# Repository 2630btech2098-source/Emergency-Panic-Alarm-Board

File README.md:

# Emergency Panic Alarm Board

**Student: Mohak Saxena**  
KiCad 10 PCB design project | Revision 1.0

## Overview

A regulated 5 V, momentary push-to-sound alarm. Holding the normally-open panic button activates an internally driven buzzer and a red warning LED. Releasing the button turns both off. There is no latching/reset function.

The supplied brief contained a conflicting water-level-indicator sentence. This project follows its Emergency Panic Alarm Board title, alarm scenario, and listed components.

## Circuit

- **J1:** 2-pin, 5.08 mm power terminal; pin 1 = +5 V and pin 2 = GND.
- **SW1:** Normally-open, 6 mm through-hole push button.
- **BZ1:** CEM-1205-IC or mechanically/electrically compatible **active 5 V** buzzer; a passive transducer is not suitable without an oscillator.
- **R1:** 330 ohms, 0.25 W axial resistor.
- **D1:** Red 5 mm LED. With an assumed 2 V forward voltage, nominal LED current is approximately 9.1 mA.

Board: **50 x 38 mm**, two copper layers, 0.6 mm tracks, through-hole components, no vias.

## Files

| File | Purpose |
| --- | --- |
| `Emergency_Panic_Alarm_Board.kicad_pro` | KiCad project |
| `Emergency_Panic_Alarm_Board.kicad_sch` | Editable schematic |
| `Emergency_Panic_Alarm_Board.kicad_pcb` | Routed PCB |
| `Mohak_Saxena_Emergency_Panic_Alarm_Board_Report.pdf` | Six-page report with schematic, routed footprints, 2D/3D views, BOM and verification |
| `Mohak_Saxena_BOM.csv` | Bill of materials exported from KiCad |
| `Mohak_Saxena_PCB_Routed.png` | PCB Editor capture |
| `Mohak_Saxena_PCB_3D.png` | KiCad 3D Viewer export |
| `Mohak_Saxena_Gerbers.zip` | Gerber layers, job file and Excellon drill files |
| `Mohak_Saxena_KiCad_Project_and_Gerbers.zip` | Downloadable project/report/fabrication package |

Open the `.kicad_pro` file in KiCad 10. Standard KiCad symbol, footprint and 3D model libraries are required. If 3D models are not found on another computer, relink their paths to that computer's KiCad model library; model paths do not affect the copper design.

## Verification

KiCad's Electrical Rules Check reported **0 errors and 0 warnings**. The PCB Design Rules Check reported **0 errors, 0 warnings, 0 unconnected items and 0 schematic/PCB parity issues**, using project/default rule settings. The board was also inspected in KiCad's 3D Viewer.

## Fabrication and testing limits

**Educational prototype only - not a certified emergency or life-safety alarm.**

No physical assembly, bench testing or sound-level measurement has been performed. There is no battery backup, fault supervision, reverse-polarity protection or latched alarm. Before fabrication, confirm the purchased components' pin spacing, polarity, switch pin grouping, voltage/current ratings, enclosure fit and manufacturer capabilities. Use a current-limited regulated 5 V source during initial testing and inspect for shorts before applying power.

The Gerber archive includes front/back copper, solder mask and silkscreen, Edge.Cuts, a Gerber job file, and separate plated/non-plated Excellon drill files. Empty paste layers are included for this through-hole design.

## Reference

[Same Sky CEM-1205-IC manufacturer datasheet](https://www.sameskydevices.com/product/resource/cem-1205-ic.pdf)

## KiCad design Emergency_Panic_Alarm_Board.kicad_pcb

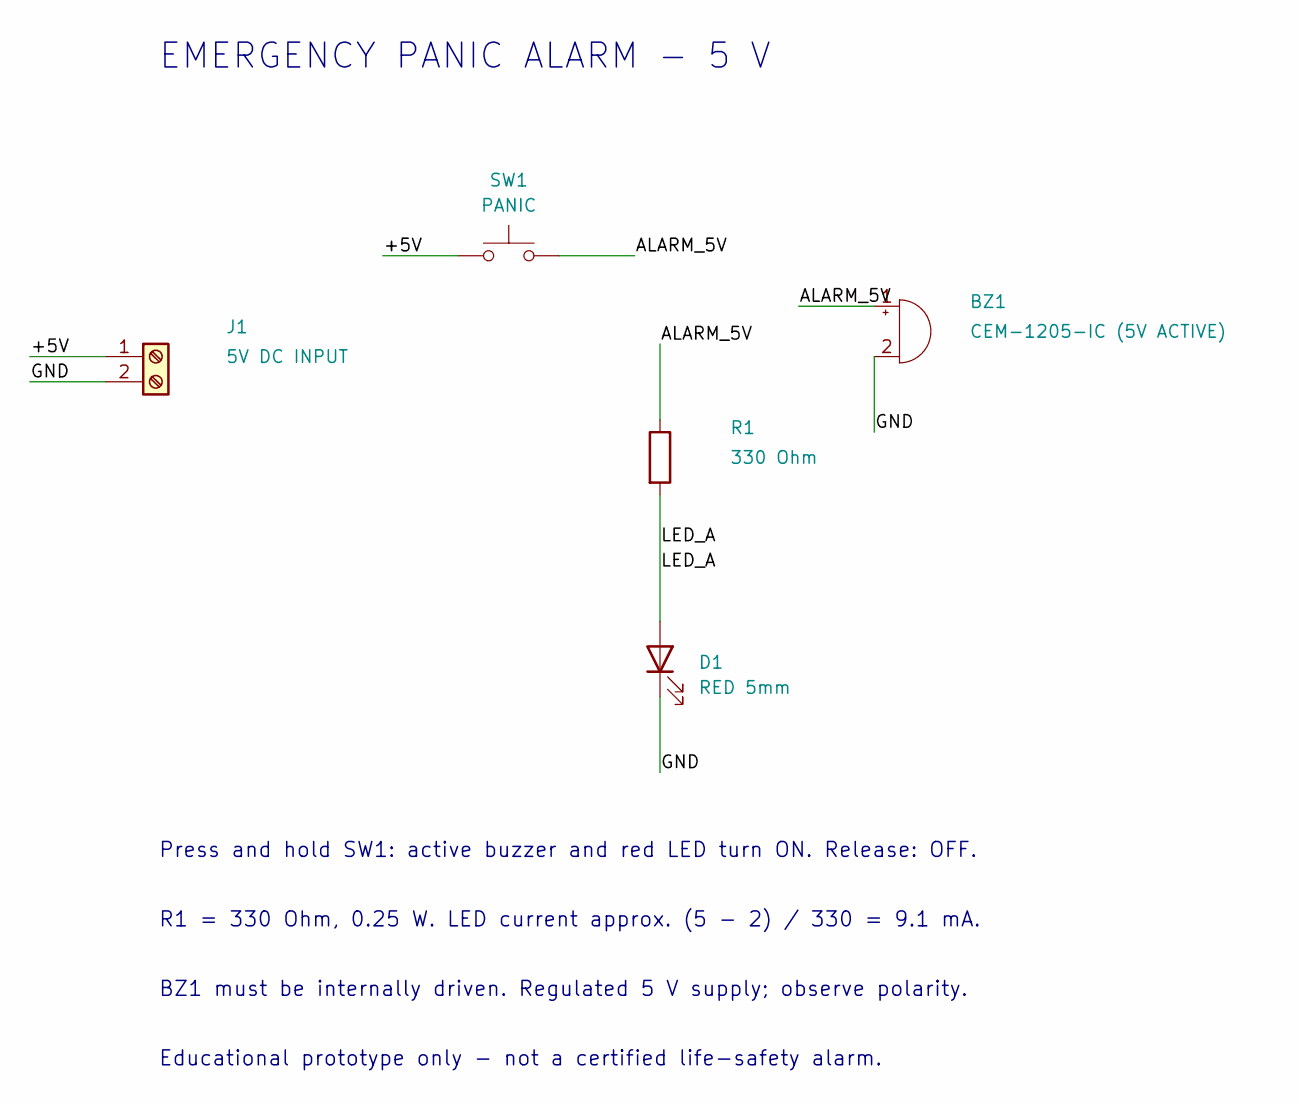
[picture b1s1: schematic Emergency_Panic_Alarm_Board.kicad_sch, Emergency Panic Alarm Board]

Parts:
BZ1: CEM-1205-IC (5V ACTIVE); Buzzer_12x9.5RM7.6
D1: RED 5mm; LED_D5.0mm
J1: 5V DC INPUT; TerminalBlock_Phoenix_MKDS-1,5-2-5.08_1x02_P5.08mm_Horizont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
R1: 330 Ohm; R_Axial_DIN0207_L6.3mm_D2.5mm_P7.62mm_Horizontal
SW1: PANIC; SW_PUSH_6mm

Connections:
/+5V: J1.1, SW1.1
/ALARM_5V: BZ1.1 (+), R1.1, SW1.2
/GND: BZ1.2 (-), D1.1 (K), J1.2
/LED_A: D1.2 (A), R1.2

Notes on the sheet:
Press and hold SW1: active buzzer and red LED turn ON. Release: OFF.
BZ1 must be internally driven. Regulated 5 V supply; observe polarity.
Educational prototype only - not a certified life-safety alarm.
EMERGENCY PANIC ALARM - 5 V
R1 = 330 Ohm, 0.25 W. LED current approx. (5 - 2) / 330 = 9.1 mA.

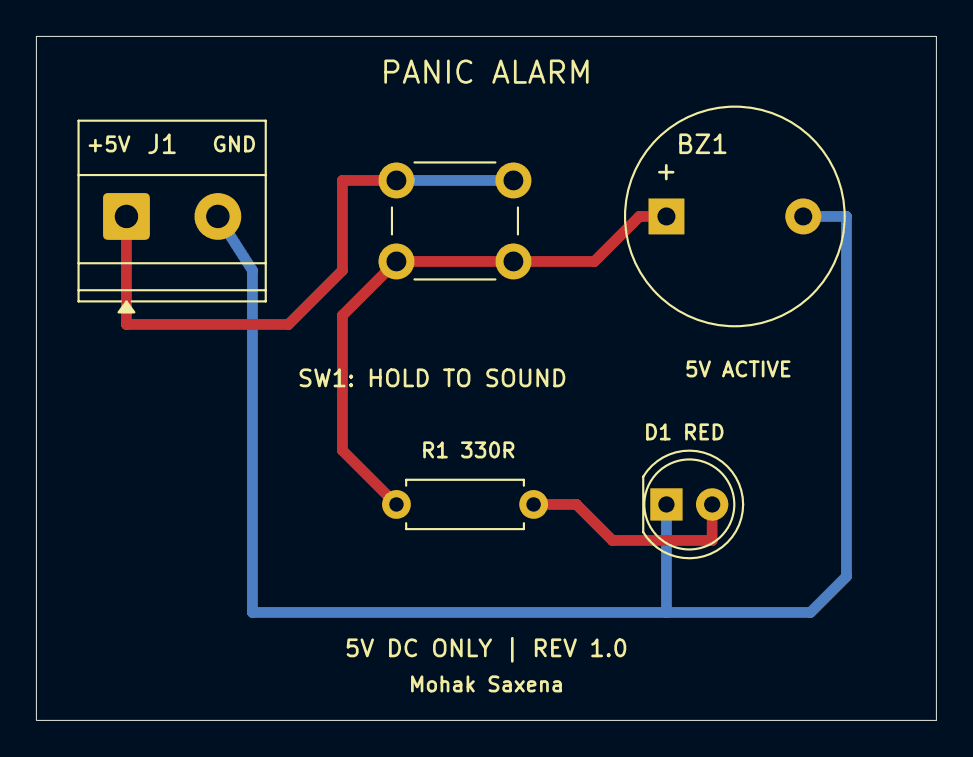
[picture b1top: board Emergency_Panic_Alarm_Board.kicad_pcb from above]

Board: 2 copper layers, 50.0 x 38.0 mm, 5 parts (0 on the bottom side), 4 nets.
